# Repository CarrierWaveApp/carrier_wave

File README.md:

# Carrier Wave

A monorepo for amateur radio QSO (contact) logging — an iOS app, a macOS companion, and shared Swift packages. Cloud synchronization to QRZ.com, Parks on the Air (POTA), and Ham2K LoFi.

## Apps

### Carrier Wave (iOS)

Full-featured QSO logger for iPhone and iPad.

- **QSO Logging** — Callsign, band, mode, frequency, RST reports, grid squares, park references, and notes
- **Multi-Service Sync** — Upload QSOs to QRZ.com, POTA, and Ham2K LoFi with per-contact sync status tracking
- **ADIF Import/Export** — Import logs from other software with intelligent deduplication
- **Dashboard** — Activity statistics by band, mode, and country with drill-down views
- **POTA Integration** — Dedicated uploads view with park grouping and upload history

### CW Sweep (macOS)

Purpose-built companion for radio hunters and contesters operating with USB-connected radios and large monitors.

- **Serial Radio Control** — CI-V (Icom), Kenwood, and Elecraft protocol support via USB serial
- **Live Spot Aggregation** — RBN, POTA, SOTA, and WWFF spots with dedup and distance enrichment
- **DX Cluster** — Telnet cluster client with spot parsing
- **Band Map** — Canvas-rendered spot visualization
- **Role-Based Layouts** — Contester, Hunter, Activator, DXer, and Casual operating modes
- **Command Palette** — Cmd+K quick access
- **Shared iCloud Store** — QSOs sync between Carrier Wave and CW Sweep via iCloud

## Requirements

- iOS 17.0+ / macOS 14.0+
- Xcode 16.0+

## Architecture

Built with SwiftUI and SwiftData. No external dependencies.

### Monorepo Structure

```
carrier_wave/
├── CarrierWave/           # iOS app (SwiftUI/SwiftData)
├── CWSweep/               # macOS companion app (xcodeproj via xcodegen)
├── CarrierWaveCore/       # SPM: protocol logic, parsers, utilities, FT8 codec
├── CarrierWaveData/       # SPM: SwiftData models, cloud sync, shared services
├── CarrierWaveTests/      # iOS app tests
├── CarrierWaveWatch/      # watchOS companion
└── CarrierWaveWidgets/    # Widget extension
```

### Shared Packages

- **CarrierWaveCore** — Protocol logic (CI-V, Kenwood), parsers (ADIF, QuickEntry, Callsign), utilities (Maidenhead, Morse, Band), FT8 codec
- **CarrierWaveData** — SwiftData models (QSO, LoggingSession, ServicePresence), cloud sync, shared services

### Key Patterns

- **Actor-based clients** for thread-safe network operations
- **Keychain storage** for credentials (never stored in SwiftData)
- **Deduplication** via 2-minute time buckets + band + mode + callsign
- **Batch uploads** (50 QSOs per batch for QRZ, park-grouped for POTA)

## Building

```bash
# Carrier Wave (iOS)
xcodebuild -project CarrierWave.xcodeproj -scheme CarrierWave \
  -destination 'platform=iOS Simulator,name=iPhone 17 Pro' build

# CW Sweep (macOS) — requires xcodegen for project generation
xcodegen generate --spec CWSweep/project.yml
xcodebuild -project CWSweep/CWSweep.xcodeproj -scheme CWSweep build
```

## Sync Services

| Service | Auth Method | Features |
|---------|-------------|----------|
| QRZ.com | Session-based | Batch ADIF upload |
| POTA | Bearer token | Park-grouped multipart upload |
| Ham2K LoFi | Email device linking | Bidirectional sync |

## License

Copyright (C) 2026 Jay Vana and contributors.

Carrier Wave is free software: you can redistribute it and/or modify it under the terms of the GNU General Public License as published by the Free Software Foundation, either version 3 of the License, or (at your option) any later version. It is distributed in the hope that it will be useful, but WITHOUT ANY WARRANTY. See [LICENSE](LICENSE) for the full text.

Bundled third-party code and assets (KISS FFT, the fonts under `hardware/` and `pebble/`, the Seeed OPL library) keep their own licenses, noted alongside those files.

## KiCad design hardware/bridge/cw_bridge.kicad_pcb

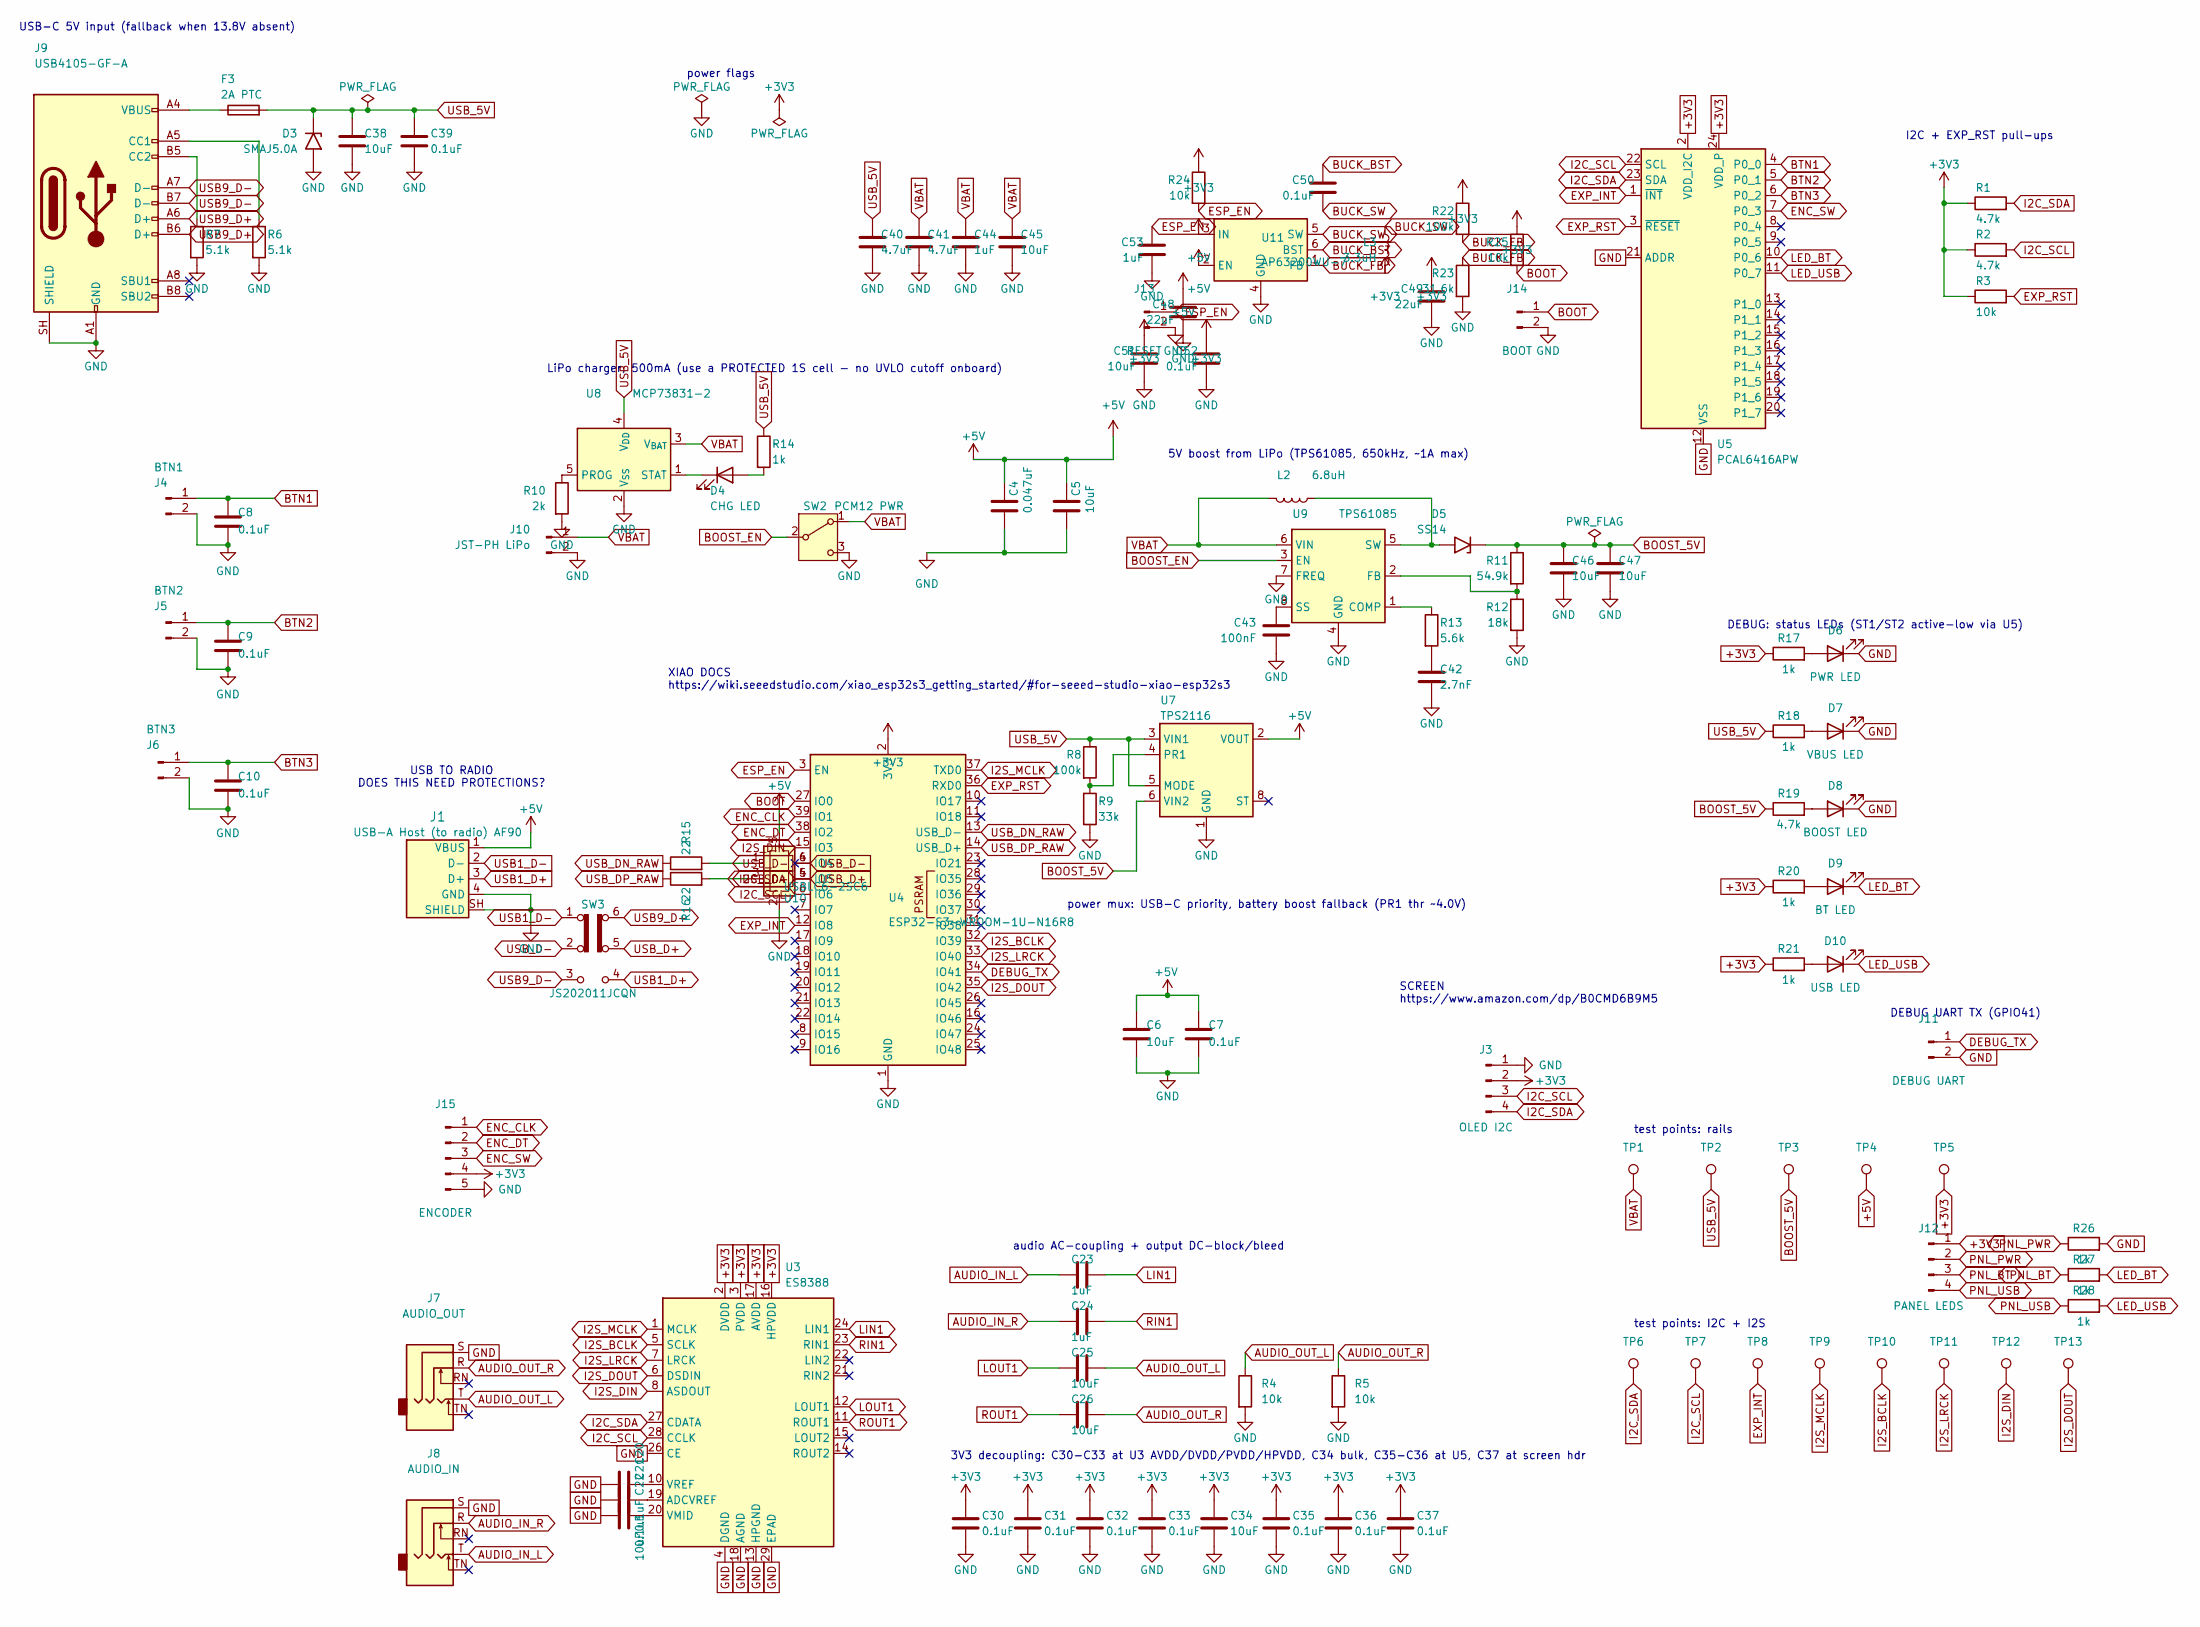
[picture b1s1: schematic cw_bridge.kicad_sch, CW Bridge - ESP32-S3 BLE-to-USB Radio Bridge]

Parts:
C4: 0.047uF; C_0402_1005Metric_Pad0.74x0.62mm_HandSolder; LCSC C307434
C5, C6, C25, C26, C34, C38, C45, C46, C47, C51: 10uF; C_0805_2012Metric_Pad1.18x1.45mm_HandSolder; LCSC C15850
C7, C8, C9, C10, C30, C31, C32, C33, C35, C36, C37: 0.1uF; C_0402_1005Metric_Pad0.74x0.62mm_HandSolder; LCSC C1525
C20, C21: 0.1uF; C_0603_1608Metric; LCSC C14663
C22: 10uF; C_0805_2012Metric; LCSC C15850
C23, C24, C44, C53: 1uF; C_0603_1608Metric_Pad1.08x0.95mm_HandSolder; LCSC C15849
C39, C50, C52: 0.1uF; C_0603_1608Metric_Pad1.08x0.95mm_HandSolder; LCSC C14663
C40, C41: 4.7uF; C_0805_2012Metric_Pad1.18x1.45mm_HandSolder; LCSC C1779
C42: 2.7nF; C_0603_1608Metric_Pad1.08x0.95mm_HandSolder; LCSC C1609
C43: 100nF; C_0603_1608Metric_Pad1.08x0.95mm_HandSolder; LCSC C14663
C48, C49: 22uF; C_0805_2012Metric_Pad1.18x1.45mm_HandSolder; LCSC C45783
D3: SMAJ5.0A; D_SMA; LCSC C113952
D4: CHG LED; LED_0603_1608Metric_Pad1.05x0.95mm_HandSolder; LCSC C2287
D5: SS14; D_SMA; LCSC C2480
D6: PWR LED; LED_0603_1608Metric_Pad1.05x0.95mm_HandSolder; LCSC C965804
D7: VBUS LED; LED_0603_1608Metric_Pad1.05x0.95mm_HandSolder; LCSC C965807
D8: BOOST LED; LED_0603_1608Metric_Pad1.05x0.95mm_HandSolder; LCSC C965799
D9: BT LED; LED_0603_1608Metric_Pad1.05x0.95mm_HandSolder; LCSC C965804
D10: USB LED; LED_0603_1608Metric_Pad1.05x0.95mm_HandSolder; LCSC C965807
F3: 2A PTC; Fuse_1206_3216Metric_Pad1.42x1.75mm_HandSolder; LCSC C545216
J1: USB-A Host (to radio) AF90; USB_A_Molex_67643_Horizontal; LCSC C456018
J3: OLED I2C; JST_PH_B4B-PH-K_1x04_P2.00mm_Vertical
J4: BTN1; JST_PH_B2B-PH-K_1x02_P2.00mm_Vertical
J5: BTN2; JST_PH_B2B-PH-K_1x02_P2.00mm_Vertical
J6: BTN3; JST_PH_B2B-PH-K_1x02_P2.00mm_Vertical
J7: AUDIO_OUT; Jack_3.5mm_CUI_SJ1-3515N_Horizontal
J8: AUDIO_IN; Jack_3.5mm_CUI_SJ1-3515N_Horizontal
J9: USB4105-GF-A; USB_C_Receptacle_GCT_USB4105-xx-A_16P_TopMnt_Horizontal; LCSC C3020560
J10: JST-PH LiPo; JST_PH_B2B-PH-K_1x02_P2.00mm_Vertical; LCSC C131337
J11: DEBUG UART; JST_PH_B2B-PH-K_1x02_P2.00mm_Vertical
J12: PANEL LEDS; JST_PH_B4B-PH-K_1x04_P2.00mm_Vertical
J13: RESET; JST_PH_B2B-PH-K_1x02_P2.00mm_Vertical
J14: BOOT; JST_PH_B2B-PH-K_1x02_P2.00mm_Vertical
J15: ENCODER; JST_PH_B5B-PH-K_1x05_P2.00mm_Vertical
L2: 6.8uH; L_Sunlord_SWPA5040S; LCSC C36411
L3: 3.3uH; L_Sunlord_SWPA5040S; LCSC C305173
R1, R2, R19: 4.7k; R_0603_1608Metric_Pad0.98x0.95mm_HandSolder; LCSC C23162
R3, R4, R5, R24, R25: 10k; R_0603_1608Metric_Pad0.98x0.95mm_HandSolder; LCSC C25804
R6, R7: 5.1k; R_0603_1608Metric_Pad0.98x0.95mm_HandSolder; LCSC C23186
R8, R22: 100k; R_0603_1608Metric_Pad0.98x0.95mm_HandSolder; LCSC C25803
R9: 33k; R_0603_1608Metric_Pad0.98x0.95mm_HandSolder; LCSC C4216
R10: 2k; R_0603_1608Metric_Pad0.98x0.95mm_HandSolder; LCSC C22975
R11: 54.9k; R_0603_1608Metric_Pad0.98x0.95mm_HandSolder; LCSC C23077
R12: 18k; R_0603_1608Metric_Pad0.98x0.95mm_HandSolder; LCSC C25810
R13: 5.6k; R_0603_1608Metric_Pad0.98x0.95mm_HandSolder; LCSC C23189
R14, R17, R18, R20, R21, R26, R27, R28: 1k; R_0603_1608Metric_Pad0.98x0.95mm_HandSolder; LCSC C21190
R15, R16: 22; R_0603_1608Metric_Pad0.98x0.95mm_HandSolder; LCSC C23345
R23: 31.6k; R_0603_1608Metric_Pad0.98x0.95mm_HandSolder; LCSC C25967
SW2: PCM12 PWR; SW_SPDT_PCM12; LCSC C221841
SW3: JS202011JCQN; SW_DPDT_CK_JS202011JCQN; LCSC C221665
TP1: VBAT; TestPoint_Pad_D1.5mm
TP2: USB_5V; TestPoint_Pad_D1.5mm
TP3: BOOST_5V; TestPoint_Pad_D1.5mm
TP4: +5V; TestPoint_Pad_D1.5mm
TP5: +3V3; TestPoint_Pad_D1.5mm
TP6: I2C_SDA; TestPoint_Pad_D1.5mm
TP7: I2C_SCL; TestPoint_Pad_D1.5mm
TP8: EXP_INT; TestPoint_Pad_D1.5mm
TP9: I2S_MCLK; TestPoint_Pad_D1.5mm
TP10: I2S_BCLK; TestPoint_Pad_D1.5mm
TP11: I2S_LRCK; TestPoint_Pad_D1.5mm
TP12: I2S_DIN; TestPoint_Pad_D1.5mm
TP13: I2S_DOUT; TestPoint_Pad_D1.5mm
U3: ES8388; QFN-28-1EP_4x4mm_P0.45mm_EP2.6x2.6mm; LCSC C365736
U4: ESP32-S3-WROOM-1U-N16R8; ESP32-S3-WROOM-1U; LCSC C3013946
U5: PCAL6416APW; TSSOP-24_4.4x7.8mm_P0.65mm; LCSC C2652299
U7: TPS2116; SOT-583-8; LCSC C3235557
U8: MCP73831-2; SOT-23-5; LCSC C424093
U9: TPS61085; VSSOP-8_3x3mm_P0.65mm; LCSC C113659
U10: USBLC6-2SC6; SOT-23-6; LCSC C7519
U11: AP63200WU-7; TSOT-23-6; LCSC C2071868

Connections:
+3V3: C30.1, C31.1, C32.1, C33.1, C34.1, C35.1, C36.1, C37.1, C49.1, C51.1, C52.1, J3.2, J12.1, J15.4, L3.2, R1.1, R2.1, R3.1, R17.1, R20.1, R21.1, R22.1, R24.1, R25.1, TP5.1, U3.2 (DVDD), U3.3 (PVDD), U3.16 (HPVDD), U3.17 (AVDD), U4.2 (3V3), U5.2 (VDD_I2C), U5.24 (VDD_P)
+5V: C4.1, C5.1, C6.1, C7.1, C48.1, J1.1 (VBUS), TP4.1, U7.2 (VOUT), U7.7 (VOUT), U10.5 (VBUS), U11.2 (EN), U11.3 (IN)
AUDIO_IN_L: C23.1, J8.T
AUDIO_IN_R: C24.1, J8.R
AUDIO_OUT_L: C25.2, J7.T, R4.1
AUDIO_OUT_R: C26.2, J7.R, R5.1
BOOST_5V: C46.1, C47.1, D5.1 (A1), R11.1, R19.1, TP3.1, U7.6 (VIN2)
BOOST_EN: SW2.2 (B), U9.3 (EN)
BOOT: J14.1, R25.2, U4.27 (IO0)
BTN1: C8.1, J4.1, U5.4 (P0_0)
BTN2: C9.1, J5.1, U5.5 (P0_1)
BTN3: C10.1, J6.1, U5.6 (P0_2)
BUCK_BST: C50.1, U11.6 (BST)
BUCK_FB: R22.2, R23.1, U11.1 (FB)
BUCK_SW: C50.2, L3.1, U11.5 (SW)
DEBUG_TX: J11.1, U4.34 (IO41)
ENC_CLK: J15.1, U4.39 (IO1)
ENC_DT: J15.2, U4.38 (IO2)
ENC_SW: J15.3, U5.7 (P0_3)
ESP_EN: C53.1, J13.1, R24.2, U4.3 (EN)
EXP_INT: TP8.1, U4.12 (IO8), U5.1 (~INT)
EXP_RST: R3.2, U4.36 (RXD0), U5.3 (~RESET)
GND: C4.2, C5.2, C6.2, C7.2, C8.2, C9.2, C10.2, C20.2, C21.2, C22.2, C30.2, C31.2, C32.2, C33.2, C34.2, C35.2, C36.2, C37.2, C38.2, C39.2, C40.2, C41.2, C42.2, C43.2, C44.2, C45.2, C46.2, C47.2, C48.2, C49.2, C51.2, C52.2, C53.2, D3.2 (A2), D6.1 (K), D7.1 (K), D8.1 (K), J1.4 (GND), J1.SH (SHIELD), J3.1, J4.2, J5.2, J6.2, J7.S, J8.S, J9.A1 (GND), J9.A12 (GND), J9.B1 (GND), J9.B12 (GND), J9.SH (SHIELD), J10.2, J11.2, J13.2, J14.2, J15.5, R4.2, R5.2, R6.2, R7.2, R9.2, R10.2, R12.2, R23.2, R26.2, SW2.3 (C), U3.4 (DGND), U3.13 (HPGND), U3.18 (AGND), U3.26 (CE), U3.29 (EPAD), U4.1 (GND), U4.40 (GND), U4.41 (GND), U5.12 (VSS), U5.21 (ADDR), U7.1 (GND), U8.2 (V_{SS}), U9.4 (GND), U9.7 (FREQ), U10.2 (GND), U11.4 (GND)
I2C_SCL: J3.3, R2.2, TP7.1, U3.28 (CCLK), U4.6 (IO6), U5.22 (SCL)
I2C_SDA: J3.4, R1.2, TP6.1, U3.27 (CDATA), U4.5 (IO5), U5.23 (SDA)
I2S_BCLK: TP10.1, U3.5 (SCLK), U4.32 (IO39)
I2S_DIN: TP12.1, U3.8 (ASDOUT), U4.15 (IO3)
I2S_DOUT: TP13.1, U3.6 (DSDIN), U4.35 (IO42)
I2S_LRCK: TP11.1, U3.7 (LRCK), U4.33 (IO40)
I2S_MCLK: TP9.1, U3.1 (MCLK), U4.37 (TXD0)
LED_BT: D9.1 (K), R27.2, U5.10 (P0_6)
LED_USB: D10.1 (K), R28.2, U5.11 (P0_7)
LIN1: C23.2, U3.24 (LIN1)
LOUT1: C25.1, U3.12 (LOUT1)
unnamed: C42.1, R13.2
unnamed: D4.2 (A), R14.2
unnamed: D4.1 (K), U8.1 (STAT)
unnamed: D5.2 (A2), L2.1, U9.5 (SW)
unnamed: D6.2 (A), R17.2
unnamed: D7.2 (A), R18.2
unnamed: D8.2 (A), R19.2
unnamed: D9.2 (A), R20.2
unnamed: D10.2 (A), R21.2
unnamed: F3.1, J9.A4 (VBUS), J9.A9 (VBUS), J9.B4 (VBUS), J9.B9 (VBUS)
unnamed: J9.A5 (CC1), R6.1
unnamed: J9.B5 (CC2), R7.1
unnamed: C21.1, U3.19 (ADCVREF)
unnamed: C22.1, U3.20 (VMID)
unnamed: C20.1, U3.10 (VREF)
unnamed: R8.2, R9.1, U7.4 (PR1)
unnamed: R10.1, U8.5 (PROG)
unnamed: R13.1, U9.1 (COMP)
unnamed: R11.2, R12.1, U9.2 (FB)
unnamed: C43.1, U9.8 (SS)
PNL_BT: J12.3, R27.1
PNL_PWR: J12.2, R26.1
PNL_USB: J12.4, R28.1
RIN1: C24.2, U3.23 (RIN1)
ROUT1: C26.1, U3.11 (ROUT1)
USB1_D+: J1.3 (D+), SW3.4 (A)
USB1_D-: J1.2 (D-), SW3.1 (A)
USB9_D+: J9.A6 (D+), J9.B6 (D+), SW3.6 (C)
USB9_D-: J9.A7 (D-), J9.B7 (D-), SW3.3 (C)
USB_5V: C38.1, C39.1, C40.1, D3.1 (A1), F3.2, R8.1, R14.1, R18.1, TP2.1, U7.3 (VIN1), U7.5 (MODE), U8.4 (V_{DD})
USB_D+: R16.2, SW3.5 (B), U10.3 (I/O2), U10.4 (I/O2)
USB_D-: R15.2, SW3.2 (B), U10.1 (I/O1), U10.6 (I/O1)
USB_DN_RAW: R15.1, U4.13 (USB_D-)
USB_DP_RAW: R16.1, U4.14 (USB_D+)
VBAT: C41.1, C44.1, C45.1, J10.1, L2.2, SW2.1 (A), TP1.1, U8.3 (V_{BAT}), U9.6 (VIN)

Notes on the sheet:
audio AC-coupling + output DC-block/bleed
XIAO DOCS https://wiki.seeedstudio.com/xiao_esp32s3_getting_started/#for-seeed-studio-xiao-esp32s3
5V boost from LiPo (TPS61085, 650kHz, ~1A max)
power flags
I2C + EXP_RST pull-ups
SCREEN https://www.amazon.com/dp/B0CMD6B9M5
3V3 decoupling: C30-C33 at U3 AVDD/DVDD/PVDD/HPVDD, C34 bulk, C35-C36 at U5, C37 at screen hdr
USB TO RADIO DOES THIS NEED PROTECTIONS?
power mux: USB-C priority, battery boost fallback (PR1 thr ~4.0V)
LiPo charger, 500mA (use a PROTECTED 1S cell - no UVLO cutoff onboard)
USB-C 5V input (fallback when 13.8V absent)
DEBUG: status LEDs (ST1/ST2 active-low via U5)
DEBUG UART TX (GPIO41)
test points: rails
test points: I2C + I2S

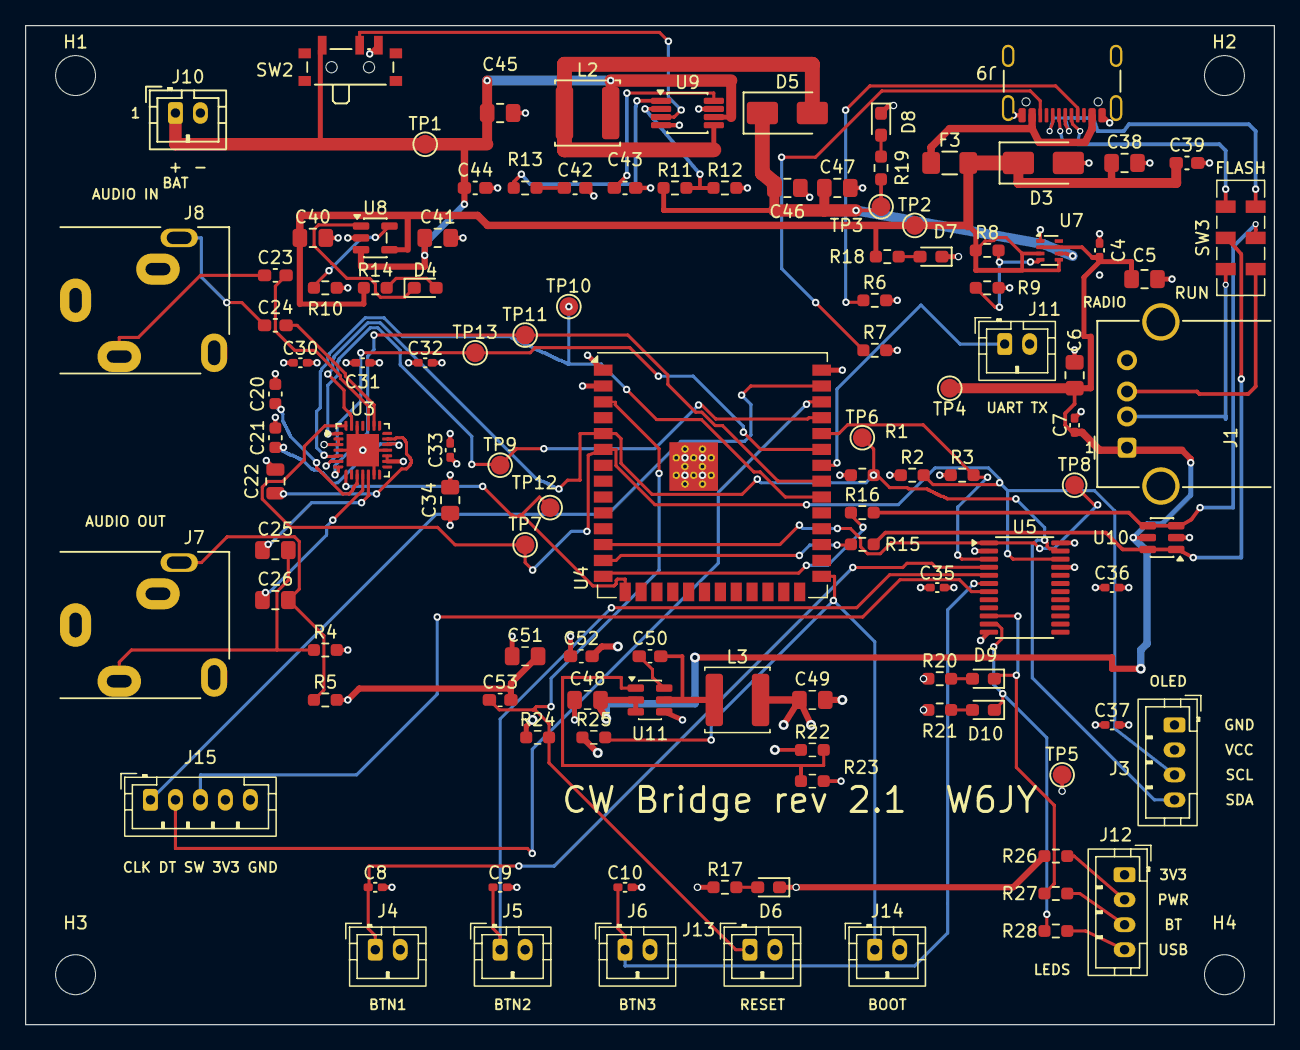
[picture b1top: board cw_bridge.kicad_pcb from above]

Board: 4 copper layers, 100.0 x 80.0 mm, 118 parts (0 on the bottom side), 69 nets.

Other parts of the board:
H1, H2, H3, H4: M3; MountingHole_3.2mm_M3

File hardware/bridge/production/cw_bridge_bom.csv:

Comment,Designator,Footprint,LCSC Part #
0.047uF,C4,C_0402_1005Metric_Pad0.74x0.62mm_HandSolder,C307434
10uF,"C5,C6,C22,C25,C26,C34,C38,C45,C46,C47,C51",C_0805_2012Metric_Pad1.18x1.45mm_HandSolder,C15850
0.1uF,"C7,C8,C9,C10,C30,C31,C32,C33,C35,C36,C37",C_0402_1005Metric_Pad0.74x0.62mm_HandSolder,C1525
0.1uF,"C20,C21,C39,C43,C50,C52",C_0603_1608Metric,C14663
1uF,"C23,C24,C44,C53",C_0603_1608Metric_Pad1.08x0.95mm_HandSolder,C15849
4.7uF,"C40,C41",C_0805_2012Metric_Pad1.18x1.45mm_HandSolder,C1779
2.7nF,C42,C_0603_1608Metric_Pad1.08x0.95mm_HandSolder,C1609
22uF,"C48,C49",C_0805_2012Metric_Pad1.18x1.45mm_HandSolder,C45783
SMAJ5.0A,D3,D_SMA,C113952
CHG LED,D4,LED_0603_1608Metric_Pad1.05x0.95mm_HandSolder,C2287
SS14,D5,D_SMA,C2480
PWR LED,"D6,D9",LED_0603_1608Metric_Pad1.05x0.95mm_HandSolder,C965804
VBUS LED,"D7,D10",LED_0603_1608Metric_Pad1.05x0.95mm_HandSolder,C965807
BOOST LED,D8,LED_0603_1608Metric_Pad1.05x0.95mm_HandSolder,C965799
2A PTC,F3,Fuse_1206_3216Metric_Pad1.42x1.75mm_HandSolder,C545216
USB-A Host (to radio) AF90,J1,USB_A_Molex_67643_Horizontal,C456018
USB4105-GF-A,J9,USB_C_Receptacle_GCT_USB4105-xx-A_16P_TopMnt_Horizontal,C3020560
JST-PH LiPo,J10,JST_PH_B2B-PH-K_1x02_P2.00mm_Vertical,C131337
6.8uH,L2,L_Sunlord_SWPA5040S,C36411
3.3uH,L3,L_Sunlord_SWPA5040S,C305173
4.7k,"R1,R2,R19",R_0603_1608Metric_Pad0.98x0.95mm_HandSolder,C23162
10k,"R3,R4,R5,R24,R25",R_0603_1608Metric_Pad0.98x0.95mm_HandSolder,C25804
5.1k,"R6,R7",R_0603_1608Metric_Pad0.98x0.95mm_HandSolder,C23186
100k,"R8,R22",R_0603_1608Metric_Pad0.98x0.95mm_HandSolder,C25803
33k,R9,R_0603_1608Metric_Pad0.98x0.95mm_HandSolder,C4216
2k,R10,R_0603_1608Metric_Pad0.98x0.95mm_HandSolder,C22975
54.9k,R11,R_0603_1608Metric_Pad0.98x0.95mm_HandSolder,C23077
18k,R12,R_0603_1608Metric_Pad0.98x0.95mm_HandSolder,C25810
5.6k,R13,R_0603_1608Metric_Pad0.98x0.95mm_HandSolder,C23189
1k,"R14,R17,R18,R20,R21,R26,R27,R28",R_0603_1608Metric_Pad0.98x0.95mm_HandSolder,C21190
22,"R15,R16",R_0603_1608Metric_Pad0.98x0.95mm_HandSolder,C23345
31.6k,R23,R_0603_1608Metric_Pad0.98x0.95mm_HandSolder,C25967
PCM12 PWR,SW2,SW_SPDT_PCM12,C221841
JS202011JCQN,SW3,SW_DPDT_CK_JS202011JCQN,C221665
ES8388,U3,QFN-28-1EP_4x4mm_P0.45mm_EP2.6x2.6mm,C365736
ESP32-S3-WROOM-1U-N16R8,U4,ESP32-S3-WROOM-1U,C3013946
PCAL6416APW,U5,TSSOP-24_4.4x7.8mm_P0.65mm,C2652299
TPS2116,U7,SOT-583-8,C3235557
MCP73831-2,U8,SOT-23-5,C424093
TPS61085,U9,VSSOP-8_3x3mm_P0.65mm,C113659
USBLC6-2SC6,U10,SOT-23-6,C7519
AP63200WU-7,U11,TSOT-23-6,C2071868

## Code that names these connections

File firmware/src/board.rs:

//! CW Bridge rev 2 PCB pin map (ESP32-S3-WROOM-1U-N16R8, `hardware/bridge/`).
//!
//! This is the single source of truth for GPIO numbers on the firmware side.
//! It must stay in lock-step with `hardware/bridge/cw_bridge.kicad_sch` and
//! the pin table in `hardware/bridge/CLAUDE.md`. Anything not listed here is
//! a no-connect on the board — do not bind it.
//!
//! ```text
//!   WROOM pin  GPIO  net          use
//!   39         1     ENC_CLK      rotary encoder phase A (native, polled)
//!   38         2     ENC_DT       rotary encoder phase B
//!   15         3     I2S_DIN      ES8388 ADC data  -> ESP
//!   5          5     I2C_SDA      shared bus: ES8388 0x10, PCAL6416A 0x20, OLED 0x3C
//!   6          6     I2C_SCL
//!   12         8     EXP_INT      PCAL6416A interrupt (open drain, unused: we poll)
//!   13/14      19/20 USB D-/D+    native USB OTG host (no GPIO config needed)
//!   27         0     BOOT         strapping pin, J14 header (firmware never touches it)
//!   32         39    I2S_BCLK
//!   33         40    I2S_LRCK
//!   34         41    DEBUG_TX     console UART TX -> J11 (set in sdkconfig.defaults)
//!   35         42    I2S_DOUT     ESP -> ES8388 DAC data
//!   37         43    I2S_MCLK     256 x fs master clock to the codec
//!   36         44    EXP_RST      PCAL6416A ~RESET (active low, R3 pull-up)
//! ```
//!
//! Slow inputs and the firmware status LEDs live on the PCAL6416A I/O
//! expander (see [`crate::expander`]): BTN1..3 = P0_0..P0_2, ENC_SW = P0_3,
//! BT LED = P0_6, USB LED = P0_7 (both sink, active low; mirrored to the
//! panel header J12 through R27/R28).
//!
//! Not on this board (the Heltec-era firmware assumed them): a VBAT ADC
//! divider, a Vext rail switch, an OLED reset line and TRS jack plug-detect
//! switches. GPIO35/36/37 belong to the module's octal PSRAM — never use them.

/// Rotary encoder phase A (native GPIO, fast edges).
pub const PIN_ENC_CLK: i32 = 1;
/// Rotary encoder phase B.
pub const PIN_ENC_DT: i32 = 2;

/// Shared I²C bus (codec + expander + OLED).
pub const PIN_I2C_SDA: i32 = 5;
pub const PIN_I2C_SCL: i32 = 6;

/// PCAL6416A interrupt output (open drain to the ESP). Currently unused —
/// the buttons task polls the expander instead.
#[allow(dead_code)]
pub const PIN_EXP_INT: i32 = 8;
/// PCAL6416A hardware reset, active low. Driven high once at boot.
pub const PIN_EXP_RST: i32 = 44;

/// I²S link to the ES8388 codec (ESP is the clock master).
pub const PIN_I2S_MCLK: i32 = 43;
pub const PIN_I2S_BCLK: i32 = 39;
pub const PIN_I2S_LRCK: i32 = 40;
pub const PIN_I2S_DOUT: i32 = 42;
pub const PIN_I2S_DIN: i32 = 3;

/// Console UART TX to the J11 debug header. Configured through
/// `CONFIG_ESP_CONSOLE_UART_TX_GPIO` in `sdkconfig.defaults`; listed here
/// only so the map is complete.
#[allow(dead_code)]
pub const PIN_DEBUG_TX: i32 = 41;

/// I²C addresses on the shared bus.
pub const I2C_ADDR_ES8388: u8 = 0x10;
pub const I2C_ADDR_PCAL6416A: u8 = 0x20;
pub const I2C_ADDR_SSD1306: u8 = 0x3C;

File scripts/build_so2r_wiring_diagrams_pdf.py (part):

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         "shared +5V and GND rails.",
         diagram_m3,
         [
            ("Heltec GPIO 4",  "BTN1 leg 1",     "yellow", "RIG 1 select."),
            ("Heltec GPIO 5",  "BTN2 leg 1",     "yellow", "RIG 2 select."),
            ("Heltec GPIO 6",  "BTN3 leg 1",     "yellow", "Band down."),
            ("Heltec GPIO 7",  "BTN4 leg 1",     "yellow", "Band up."),
            ("All button leg 2",  "Shared GND bus -> Heltec GND", "black", "One bus, one wire to Heltec."),
            ("Heltec GPIO 2",  "LED1 DIN",       "green",  "Chain start."),
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
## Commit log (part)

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2026-02-21 Add automated database backup system with restore and iCloud sync
    Three-layer backup system protecting against data loss:
    - Layer 1: Rolling on-device snapshots in Library/Backups/ triggered on
    app launch, pre-sync, pre-import, and manual. WAL checkpoint ensures
    consistent copies. Retention: 5 most recent, preserving at least one
    per trigger type.
    - Layer 2: iCloud Drive sync copies the 2 most recent snapshots to the
2026-02-21 Fix logger inline edit using stale lookup result for wrong callsign
    When editing a QSO callsign in the logger, lookupResult could contain
    data from the previous callsign if the user typed quickly and hit Update
    before the debounced lookup (800ms) completed. Now verify that
    lookupResult.callsign matches the new callsign before using it;
    otherwise fall through to the async fetch path.
    https://claude.ai/code/session_012T9zkjgtBge9xrsrWdZehW
2026-02-21 Add QSO editing from Logs tab
    Add an Edit button to QSODetailView that presents QSOEditSheet,
    allowing users to modify QSO fields (callsign, band, mode, frequency,
    timestamp, RST, grids, parks, SOTA ref, power, location, and notes).
    Edits set cloudDirtyFlag for iCloud sync.
    https://claude.ai/code/session_01FgeUbMAgSmQTsSZ6squ42W
2026-02-21 Add design document for enriched SDR recording interactive view
    Covers karaoke-style time-aligned CW transcription, QSO span visualization
    on the waveform, segment metadata labels, and tap-to-share annotated clips.
    https://claude.ai/code/session_01ChTK7i3Zuff1iY7uKCnxXg
2026-02-22 Add tap-to-edit QSOs in session detail view
    Replace DisclosureGroup expand/collapse with tap to open QSOEditSheet.
    Rows now open the full edit form (with callsign lookup) on tap, while
    keeping swipe-to-delete on trailing edge.
    https://claude.ai/code/session_0189R5fdwHHANdDpCiHY7hW4
2026-02-24 Add custom callsign toggle for LoTW, Club Log, and LoFi service setup
    Some users have service accounts registered under a different callsign
    than their current one (e.g., a previous call before upgrading). This
    adds a "Use a different callsign" toggle to the login/setup forms for
    LoTW, Club Log, and LoFi — the three services where the login identity
    is a callsign.
    By default, the user's profile callsign is shown as read-only. When the
2026-02-25 Add spot-vs-QSO contact validation with edit distance matching
    Compare session spot callsigns against logged QSOs using Levenshtein
    edit distance <= 2. When a spot is close but not an exact match to a
    logged contact, show a dismissible yellow banner suggesting the operator
    may have copied the callsign wrong. Tapping a mismatch row opens the
    QSO editor pre-filled with the spotted callsign.
    - CallsignEditDistance: public Levenshtein distance utility in CarrierWaveCore
2026-02-26 fix: restore .fixedSize() on region pill rows to fix malformed session list layout
    The previous ViewThatFits fix (ebeeab6) removed .fixedSize() along with
    ViewThatFits, but .fixedSize() was needed to prevent SwiftUI from
    compressing the pill HStacks. Without it, pills collapsed into thin
    horizontal lines and text wrapped vertically. The crash was caused by
    ViewThatFits + .fixedSize() together, not .fixedSize() alone.
    Also adds .lineLimit(1) to power/WPM/mode pills in SessionRow statusRow
2026-02-26 feat: add ADIF comment park ref safeguards for import and export
    Import safeguards:
    - Add CommentParkAction setting (ignore / their park / my park) in
    Settings > Data & Tools > Import Behavior to control how park
    references found in ADIF COMMENT fields are handled
    - Apply setting across all import paths: file import, QRZ sync,
    and background QSO processing actor
2026-02-26 fix: scope POTA worked-before checks to previous UTC day only
    The WorkedBeforeCache was querying all-time QSOs for each callsign,
    making the "previously worked" indicator on spot rows show bands from
    any date. POTA contacts reset per UTC day, so only the previous UTC
    day is relevant for the previous-bands display.
    https://claude.ai/code/session_018dRMTiLYAH1nFsSNrfK35r
2026-02-27 fix: QRQ Crew spot bugs and dashboard brag sheet badge
    - Fix duplicate member numbers in QRQ Crew spot text (name already
    contained #NN, was appended again by displayLabel)
    - Change spot URL from carrierwave.app to qrqcrew.club
    - Add "Under Construction" badge to dashboard brag sheet card
    https://claude.ai/code/session_01XQh2nTTxWRgAusJpGBKHVR
2026-02-28 Refine brag sheet share card map: trace lines and pin markers
    Add geodesic trace lines from operator grid to each QSO cluster for a more
    defined visual connection. Replace large glowing circle markers with smaller
    traditional pin-shaped markers (needle + head) using muted colors for less
    contrast against the map background.
    https://claude.ai/code/session_015hf4wCDnop9GzDnYnHmmNn
2026-02-28 Add radio connection (CAT control) research and design document
    Deep research into adding CAT control to the iPad app. Covers
    USB serial feasibility (not practical on iPadOS), WiFi/network
    alternatives (Icom CI-V over UDP, hamlib rigctld), Bluetooth
    options, protocol specifications, UX mockups, and phased
    implementation plan. Recommends starting with Icom IC-705 WiFi.
    https://claude.ai/code/session_012TFiCfu5b9p9KQqkkfvfjz
2026-03-01 Add ESP32 WiFi bridge section to radio connection design
    Research and document ESP32 as a universal WiFi-to-serial CAT bridge
    for iPad connectivity. Covers transparent bridge vs protocol bridge
    architecture, existing firmware options (ESP32-Serial-Bridge, SOTAcat),
    hardware BOM (~$10), protocol comparison (TCP vs WebSocket vs REST vs
    BLE), and updated implementation phases. Also resolves SOTAcat API
    question and adds new open questions about firmware strategy and BLE mode.
2026-03-01 Add SCP callsign database implementation plan
    Outlines the architecture for integrating MASTER.SCP from
    supercheckpartial.com: SCPDatabase (CarrierWaveCore), SCPService
    (download/cache), logger integration (suggestions + confidence
    indicator + did-you-mean), and settings toggle.
    https://claude.ai/code/session_01Fz6KiSmN8PC62PRQ9nX7fF
2026-03-01 Augment SCP database with user's repeat contacts
    Callsigns the user has worked 2+ times are merged into the SCP
    database at startup. This catches callsigns not in MASTER.SCP
    (new hams, rare calls, club stations) that the user regularly
    contacts.
    - Add SCPDatabase.merging(additionalCallsigns:) for combining sources
    - Add SCPService.loadUserCallsigns(container:) with background
2026-03-02 Add WWFF reference directory cache with autocomplete entry field, search/nearby picker, and External Data settings
    - WWFFReference model for directory entries (reference, name, coords, country)
    - WWFFReferencesCache actor downloading wwff.co/wwff-data/wwff_directory.csv
    with word-indexed search, nearby lookup, 30-day TTL
    - WWFFReferenceEntryField with live name resolution, removable chip, search picker
    - WWFFReferencePickerSheet with nearby-by-GPS, full-text search, QSO stats
    - Replace plain TextField in SessionStartSheet with rich entry field
2026-03-03 Change activity grid hunter log icon to scope
    Match the hunter log's scope icon in the activity grid popover tooltip
    instead of list.bullet.
    https://claude.ai/code/session_0199qkNTrYDQYtrPzWLEvGjs
2026-03-03 Update Tune In design doc with resolved decisions
    Resolved 7 design decisions from discussion:
    - No dedicated tab (swipe action sufficient)
    - No background audio (kill connection on background)
    - Cellular data warning on first use
    - Single tune-in only
    - Entry point in hunter log, standalone from logger
2026-03-03 Add Tune In feature — listen to spotted activations via KiwiSDR
    Phase 1 implementation of the Tune In feature:
    - TuneInManager: standalone session coordinator with smart receiver
    auto-selection (activator-proximity sorted), cellular data warning,
    and auto-disconnect on app background
    - TuneInMiniPlayerView: persistent Apple Music-style bottom bar with
    live indicator, callsign/frequency, mute/close controls
2026-03-03 Add Tune In smart features: QSY detection, receiver monitoring, follow activator (Phase 4)
    - Auto-retune on QSY detection via RBN polling with orange alert banner and retune/dismiss buttons
    - Receiver quality monitoring suggests better KiwiSDR when SNR degrades (blue suggestion banner)
    - Follow activator bell toggle persisted to UserDefaults for tracking across sessions
    - Split expanded player smart feature UI into extension file to stay within line limits
    https://claude.ai/code/session_01A5KPS9139G4xTSv66zso4b
2026-03-04 Update logger tour plan with resolved design decisions
    - SessionStartSheet is explorable during tour
    - Tour guide is KI5GTR (actual operator), not a fictional character
    - User-driven pacing with Next/Got it buttons
    - Replay from Settings only
    - Portrait-only on iPhone, landscape supported on iPad
    https://claude.ai/code/session_018yskD1qSWgfVLfhEwFjJ6M
2026-03-04 Detect callsign owner changes by cross-referencing QRZ and HamDB
    When looking up a callsign, QRZ updates quickly with the new owner's
    name but HamDB (FCC-sourced) can lag behind. This adds parallel HamDB
    name lookups during callsign resolution to detect mismatches and
    surface an "HamDB is still updating" note in the logger card, CW info
    card, and About Me profile refresh.
    https://claude.ai/code/session_011KNDS6Nc3WnSwRqX9iSqS7
2026-03-04 Add states worked signal mosaic to session detail view
    New 10×5 grid visualization showing US states worked during a session.
    Cells glow green with intensity proportional to QSO count. Tap any
    worked state to see callsigns in a popover. Section only appears when
    at least one QSO has state data.
    https://claude.ai/code/session_0151kDPYTietpLtefS7uZW53
2026-03-04 Fix interactive tour not showing after session start
    The interactive logger tour's fullScreenCover was silently dropped by SwiftUI
    because it tried to present while the SessionStartSheet (from SessionsIdleView)
    was still mid-dismissal. Added a 600ms delay in the .task to let SwiftUI
    finish the sheet dismissal before presenting the tour overlay.
    https://claude.ai/code/session_011RxYb9iEko4PV5odpM7beC
2026-03-05 Implement qsy:// URI scheme for inter-app ham radio interoperability
    Add support for the QSY URI specification (https://github.com/jsvana/qsy-uri)
    which enables interoperability between amateur radio applications via deep links.
    Supported actions:
    - spot: Pre-fill logging form from spot data (callsign + freq required)
    - tune: Direct CAT-capable radio to change frequency/mode (freq required)
    - lookup: Open callsign information view (callsign required)
2026-03-05 Wire up all QSY URI downstream integrations
    - Spot (qsy://spot): pre-fills logger callsign, frequency, mode, notes
    - Tune (qsy://tune): updates session frequency + sends to BLE radio
    - Lookup (qsy://lookup): populates Logs tab search field with callsign
    - Log (qsy://log): shows confirmation sheet with all QSO fields, logs on confirm
    New files: QSYLogConfirmation model, QSYLogConfirmationSheet view
    https://claude.ai/code/session_01RuKDCMwtQh2mBTtjWvrNVe
2026-03-06 Fix Hunter Log spots not restarting and add landscape layout
    Spots stopped loading when navigating away from Hunter Log and back
    because .task had a guard that prevented re-execution while onDisappear
    had already stopped monitoring. Added .onAppear to restart monitoring
    when returning to the view.
    Added two-pane landscape layout (quick log + header on left, spots on
    right) matching the Logger's landscape pattern.
2026-03-06 Add Discord webhook notification for commits
    GitHub Action that posts an embed to Discord on every push,
    using the DISCORD_WEBHOOK_URL repository secret.
    https://claude.ai/code/session_01HWNZuetPPpDeRpZupouVwm
2026-03-07 Fix LoTW sync failing on first attempt due to transient SSL errors
    Add automatic retry with exponential backoff (2s, 4s, 8s) for transient
    URLErrors including SSL certificate failures, connection resets, and
    timeouts. LoTW's server occasionally returns invalid certificates on
    the first connection attempt.
    https://claude.ai/code/session_01UDcPkRSGZpinxgcW7Yc3kX
